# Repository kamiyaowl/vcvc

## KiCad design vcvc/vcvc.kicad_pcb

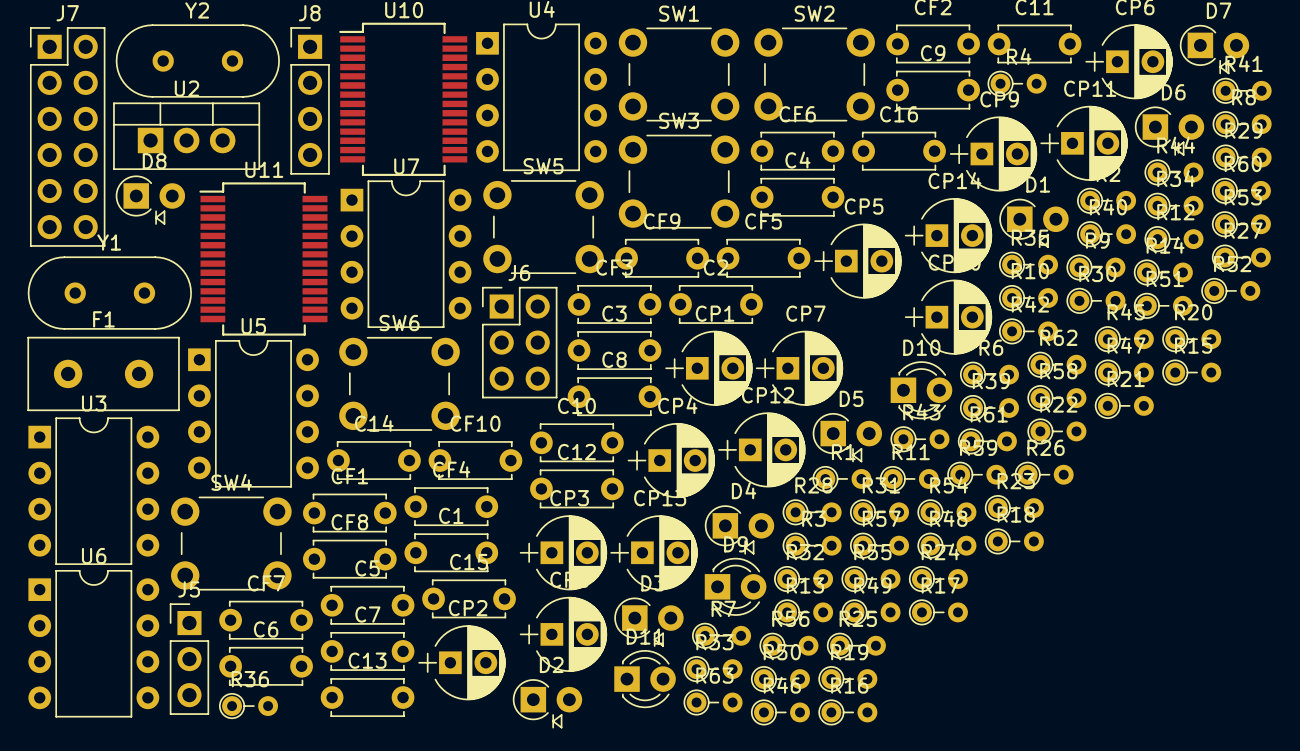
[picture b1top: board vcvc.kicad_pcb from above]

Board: 2 copper layers, 132 parts (0 on the bottom side), 98 nets, no tracks yet.

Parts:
C1, C2: 0.33uF; C_Disc_D5.0mm_W2.5mm_P5.00mm
C3, C4: 0.1uF; C_Disc_D5.0mm_W2.5mm_P5.00mm
C5, C6, C7, C8, C9, C10, C11, C12: 1uF; C_Disc_D5.0mm_W2.5mm_P5.00mm
C13, C14, C15, C16: 22pF; C_Disc_D5.0mm_W2.5mm_P5.00mm
CF1, CF3, CF5, CF6: 0.01uF; C_Disc_D5.0mm_W2.5mm_P5.00mm
CF2, CF4, CF7, CF8, CF9, CF10: 0.1uF; C_Disc_D5.0mm_W2.5mm_P5.00mm
CP1, CP2, CP3, CP4, CP5, CP6, CP7, CP8, CP9, CP10, CP11, CP12, CP13, CP14: 10uF; CP_Radial_D5.0mm_P2.50mm
D1, D2, D3, D4, D5, D6, D7, D8: 1N4148; D_A-405_P2.54mm_Vertical_AnodeUp
D9: USB2_ACTIVE; LED_D3.0mm
D10: USB1_ACTIVE; LED_D3.0mm
D11: PWR_LED; LED_D3.0mm
F1: Fuse; C_Disc_D10.5mm_W5.0mm_P5.00mm
J5: PWR_SEL; Pin_Header_Straight_1x03_Pitch2.54mm
J6: PWR_5VD; Pin_Header_Straight_2x03_Pitch2.54mm
J7: USB1_IN_SELECTOR; Pin_Header_Straight_2x06_Pitch2.54mm
J8: USB2_IN_EXT; Pin_Header_Straight_1x04_Pitch2.54mm
R1, R10: 4k7; R_Axial_DIN0204_L3.6mm_D1.6mm_P2.54mm_Vertical
R2, R7, R13, R16, R17, R18, R19, R20, R21, R22, R23, R24, R25, R28, R29, R30, R31: 1k; R_Axial_DIN0204_L3.6mm_D1.6mm_P2.54mm_Vertical
R3, R26: 100; R_Axial_DIN0204_L3.6mm_D1.6mm_P2.54mm_Vertical
R4, R27, R55, R56, R57: 10k; R_Axial_DIN0204_L3.6mm_D1.6mm_P2.54mm_Vertical
R6, R32: 470; R_Axial_DIN0204_L3.6mm_D1.6mm_P2.54mm_Vertical
R8, R9, R49, R50, R58, R59, R60, R61, R62, R63: 1k5; R_Axial_DIN0204_L3.6mm_D1.6mm_P2.54mm_Vertical
R11, R12, R14, R15, R41, R42: 100k; R_Axial_DIN0204_L3.6mm_D1.6mm_P2.54mm_Vertical
R33, R34, R35, R36: 33k; R_Axial_DIN0204_L3.6mm_D1.6mm_P2.54mm_Vertical
R39, R40: 47; R_Axial_DIN0204_L3.6mm_D1.6mm_P2.54mm_Vertical
R43, R44, R45, R46: 5k1; R_Axial_DIN0204_L3.6mm_D1.6mm_P2.54mm_Vertical
R47, R48, R51, R52: 22; R_Axial_DIN0204_L3.6mm_D1.6mm_P2.54mm_Vertical
R53, R54: 1M; R_Axial_DIN0204_L3.6mm_D1.6mm_P2.54mm_Vertical
SW1, SW2: HID0; SW_PUSH_6mm
SW3, SW4: HID1; SW_PUSH_6mm
SW5, SW6: HID2; SW_PUSH_6mm
U2: NJM7905; TO-220-3_Vertical
U3, U4, U6, U7: NJM5532; DIP-8_W7.62mm
U5: NJM4556; DIP-8_W7.62mm
U10, U11: pcm2900c; SSOP-28_5.3x10.2mm_Pitch0.65mm
Y1, Y2: 12MHz; Crystal_HC49-4H_Vertical

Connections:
+3.3VA: C3.1, D1.1, D3.1, D5.1, D7.1, R1.1, R9.1, R10.1, U3.8, U4.8, U5.8
+5VD: C1.1, C2.2, F1.1, J6.1, J6.3, J6.5, R55.1, U2.2, U10.3, U11.3
-5VA: C4.2, D2.2, D4.2, D6.2, D8.2, U2.3, U3.4, U4.4, U5.4
/HP_OUT_L: R39.1, R41.2
/HP_OUT_R: R40.1, R42.2
/LINE_L: CP2.2, D3.2, D4.1, R11.2, R19.2
/LINE_R: CP3.2, D7.2, D8.1, R12.2, R23.2
/MIC_IN_L: J7.9, R1.2, R2.2
/MIC_IN_R: J7.11, R10.2, R13.2
/MIC_POST_L: CP4.1, J7.1, J7.3, U3.1
/MIC_POST_R: CP5.1, J7.5, J7.7, U3.7
/OP_IN_L: CF2.2, D1.2, D2.1, R4.2, U3.3
/OP_IN_R: CF4.2, D5.2, D6.1, R27.2, U3.5
/SIDETONE_L: R16.2, U7.1
/SIDETONE_R: R20.2, U7.7
/USB1_HID0: SW1.1, U11.5
/USB1_HID1: SW3.1, U11.6
/USB1_HID2: SW5.1, U11.7
/USB1_IN_L: CF9.2, J7.2, J7.6, J7.10
/USB1_IN_R: CF7.2, J7.4, J7.8, J7.12
/USB1_OUT_L: CP11.2, R17.2
/USB1_OUT_R: CP13.2, R21.2
/USB1_VBUS: J5.3, R56.1
/USB1_~SSPND: R58.2, R60.2, R62.2, U11.28
/USB2_HID0: SW2.1, U10.5
/USB2_HID1: SW4.1, U10.6
/USB2_HID2: SW6.1, U10.7
/USB2_IN_L: CF10.2, J8.2
/USB2_IN_R: CF8.2, J8.3
/USB2_OUT_L: CP12.2, R18.2
/USB2_OUT_R: CP14.2, R22.2
/USB2_VBUS: J5.1, R57.1
/USB2_~SSPND: R59.2, R61.2, R63.2, U10.28
GND: C1.2, C2.1, C3.2, C4.1, C5.2, C6.2, C7.2, C8.2, C9.2, C10.2, C11.2, C12.2, C13.2, C14.2, C15.2, C16.2, CF1.2, CF3.2, CP1.2, CP6.2, CP7.2, CP8.2, CP9.2, CP10.2, D9.1, D10.1, D11.1, J6.2, J6.4, J6.6, J8.1, J8.4, R4.1, R7.1, R11.1, R12.1, R14.1, R15.1, R27.1, R41.1, R42.1, R43.1, R44.1, R45.1, R46.1, U2.1, U4.3, U4.5, U5.3, U5.5, U6.3, U6.5, U7.3, U7.5, U10.4, U10.11, U10.18, U10.22, U10.24, U10.26, U11.4, U11.11, U11.18, U11.22, U11.24, U11.26
unnamed: C5.1, U11.17
unnamed: C6.1, U10.17
unnamed: C7.1, U11.19
unnamed: C8.1, U10.19
unnamed: C9.1, U11.23
unnamed: C10.1, U10.23
unnamed: C11.1, R49.2, U11.8, U11.9, U11.27
unnamed: C12.1, R50.2, U10.8, U10.9, U10.27
unnamed: C13.1, R53.2, U11.20, Y1.1
unnamed: C14.1, R54.2, U10.20, Y2.1
unnamed: C15.1, R53.1, U11.21, Y1.2
unnamed: C16.1, R54.1, U10.21, Y2.2
unnamed: CF1.1, CF2.1, R2.1
unnamed: CF3.1, CF4.1, R13.1
unnamed: CF5.1, R28.1, R35.1, U4.1
unnamed: CF5.2, R16.1, R17.1, R18.1, R19.1, R28.2, U4.2
unnamed: CF6.1, R29.1, R36.1, U4.7
unnamed: CF6.2, R20.1, R21.1, R22.1, R23.1, R29.2, U4.6
unnamed: CF7.1, U11.13
unnamed: CF8.1, U10.13
unnamed: CF9.1, U11.12
unnamed: CF10.1, U10.12
unnamed: R49.1, R51.2
unnamed: R50.1, R52.2
unnamed: CP1.1, R3.2
unnamed: CP4.2, R14.2, R24.2
unnamed: CP5.2, R15.2, R25.2
unnamed: CP6.1, R26.2
unnamed: CP7.1, U11.10
unnamed: CP8.1, U10.10
unnamed: CP9.1, U11.14
unnamed: CP10.1, U10.14
unnamed: CP11.1, U11.16
unnamed: CP12.1, U10.16
unnamed: CP13.1, U11.15
unnamed: CP14.1, U10.15
unnamed: D9.2, R57.2
unnamed: D10.2, R56.2
unnamed: D11.2, R55.2
unnamed: F1.2, J5.2
unnamed: R3.1, R6.2, U3.2
unnamed: R7.2, R8.2
unnamed: R8.1, R9.2
unnamed: R24.1, R30.2, U6.2
unnamed: R25.1, R31.2, U6.6
unnamed: R26.1, R32.2, U3.6
unnamed: R30.1, R33.1, U6.1
unnamed: R31.1, R34.1, U6.7
unnamed: R33.2, U7.2
unnamed: R34.2, U7.6
unnamed: R35.2, U5.2
unnamed: R36.2, U5.6
unnamed: R39.2, U5.1
unnamed: R40.2, U5.7
unnamed: R47.1, U11.2
unnamed: R48.1, U10.2
unnamed: R51.1, U11.1
unnamed: R52.1, U10.1
unnamed: R58.1, SW1.2
unnamed: R59.1, SW2.2
unnamed: R60.1, SW3.2
unnamed: R61.1, SW4.2
unnamed: R62.1, SW5.2
unnamed: R63.1, SW6.2

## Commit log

2019-01-22 電源回路と入力書いた
2019-01-22 MIC Lch書いた
2019-01-22 一部修正
2019-01-22 pcm2900c追加
2019-01-24 mic preampシミュレーションで定数修正
2019-01-24 マイクプリアンプの回路を反映
2019-01-24 USB1回路目を書いた
2019-01-24 2回路目も書いた
2019-01-24 3.3VAを4Vにした（？）
2019-01-24 HP Amp回路も書いた
2019-01-25 入力保護追加
2019-01-25 sidetone回路を追加
2019-01-25 すでに存在するシンボルは割り当てた
2019-01-25 とりあえず基盤にインポート
2019-01-26 Close #1 : USB2, LINE INの信号はUSB1電源で差動で受けるように変更
